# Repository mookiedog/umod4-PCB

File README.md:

# umod4-PCB

The Ultramod4 (A.K.A [umod4](https://github.com/mookiedog/umod4)) project is a real-time datalogger for Aprila Gen 1 ECUs.
It replaces the EPROM in an Aprila Gen 1 ECU with a circuit board that replaces the EPROM with a fast CPU that emulates an EPROM.
The EPROM emulation CPU's flash contains a special data logging firmware that the ECU will run.
The data-logging firmware is modified to send a real-time stream of ECU data to an interface on the umod4-PCB.
Software running in a daughterboard on the umod4-PCB combines the incoming ECU data stream with real-time GPS location and velocity information.
The combined data stream gets written to a logfile on a micro SD card.

The complete project is made up of:

* [umod4](https://github.com/mookiedog/umod4): the repository containing all the software that runs on the umod4-PCB.
* [UM4](https://github.com/mookiedog/umod4/tree/main/ecu/src): a special data logging firmware that runs inside the Gen1 ECU, currently resides inside the umod4 repository
* umod4-PCB: this repository, containing the PCB design files

The view below shows a top view of the 4V1a PCB, currently the most recent design.
The board's strange shape and cutout are mostly required to access ECU mounting points while avoiding interference with tall components on the ECU itself.

## PCB Status

The first version of the board (marked '4V0b' on its silkscreen) was fabricated at JCLPCB in 2022 and tested.
The second revision, the 4V1a board, was produced by JLCPCB in Jan 2025.
It incorporates all the workarounds from 4V0b, plus a number of changes and enhancements discovered over the last 18 months.
See the file [ChangeList.md](ChangeList.md) for the complete set of changes incorporated by 4V1.

The 4V1 version PCB has passed all its tests so far.

## Goals

### Design For Manufacture

This project uses a bare RP2040 chip to emulate the EPROM in a Gen 1 ECU.
The chip is too difficult for me to place by hand for reflowing the board using my [home-brew reflow](https://github.com/mookiedog/Reflow) process.
Instead, this PCB is designed for fabrication at JLCPCB.com.
Where possible, the BOM parts were chosen from JLCPCB's "basic" component list to avoid the fee for using an "extended" component.
Even so, stocks of "basic" parts fluctuate and components become obsolete, so the BOM might change with time to accomodate those changes.

Once any requirement for hand assembly was eliminated, the door was open to use smaller 0402 components on the PCB.

The initial version of the design (4V0b) has proven it can go end-to-end through the entire JCLPCB fabrication process where the resulting boards function as designed.

### Accessibility

I am not interested in making this project into a product that I would sell and support.
That said, it may be interesting enough for other Aprilia owners out there who have software and/or hardware skills that they might want to replicate the project for their own bike.

Who knows, it might be one of those things where a batch of boards gets made from time to time for people who are interested, feel like participating, and know that it is not a product.
Seriously, the last thing on earth that I want is someone sending me a note complaining that I haven't got WiFi working yet.

## Design Tool Choice

The project is currently developed using Cadsoft Eagle version 7.6, the last version I got years ago.
It's because I've used Eagle for the last bazillion years, and I own that old version outright.
These days, you are forced to forced to buy new versions of Eagle on a monthly subscription basis.
That doesn't work for me, because I make no money off this stuff and can't afford the subscription fees.
Too bad, I like Eagle.

I realize that at some point it would be worth switching the design over to something like KiCad to make it more accessible to the open source community.

Someday.

## Project Status

A ton of software exists, and a ton is left to write.

That said, the key to going for a ride though is that the fake EPROM on the circuit board needs to work. And it does!

Below, is a scope shot of the ECU performing memory cycles.
The top trace is the E clock generated by the ECU processor (a MC68HC11 variant).
The bottom trace is generated by the firmware that is pretending to be an EPROM.
The bottom trace goes high when the fake EPROM firmware reads the address and control signals from the HC11 memory bus.

If the memory cycle does not target the EPROM, the firmware drives the lower trace back to zero again very shortly after reading the address and control signal info.

If the memory cycle targets the EPROM with a read operation, the firmware takes a bit more time to access the proper memory byte corresponding to the desired EPROM memory byte, then drive that data onto the memory bus.
The lower scope trace gets driven low again to indicate the time that the read data is available on the memory bus.

Finally, if the memory cycle targets the EPROM with a write, the firmware is required to wait even longer for the write data to finally appear on the bus.
The fake EPROM firmware drives the lower trace back to zero to indicate the exact time that it samples the write data off the HC11 memory bus.

Given that all of these operations are going on all the time, the lower trace has been set up so that it shows examples of the three different operations (ignore, read, write) superimposed on each other:

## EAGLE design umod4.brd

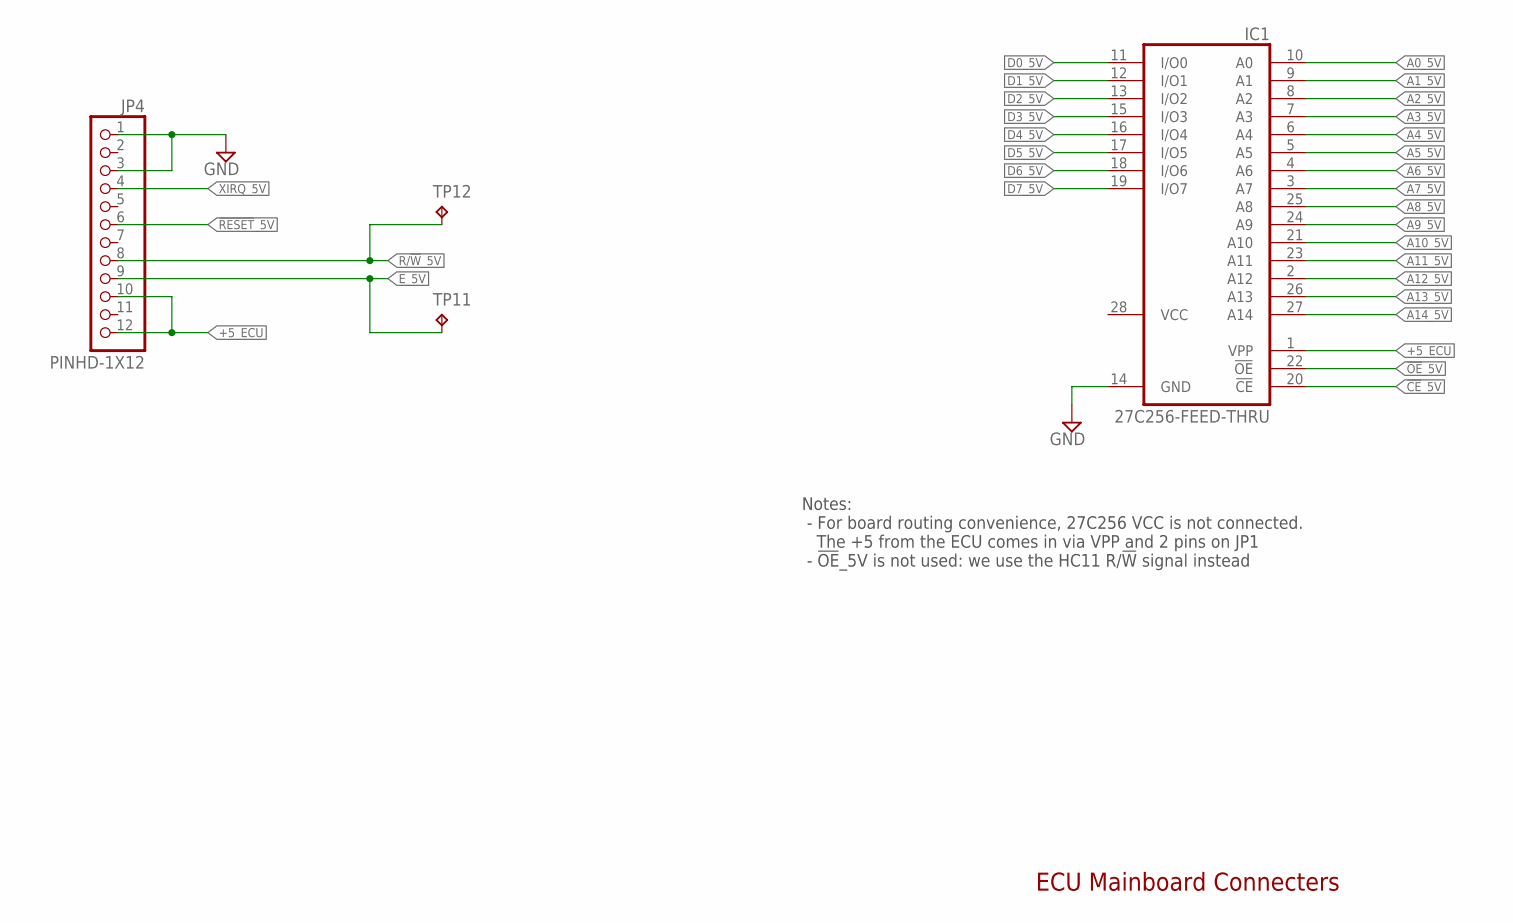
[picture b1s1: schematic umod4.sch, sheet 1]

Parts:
IC1: 27C256-FEED-THRU; DIL28-6
JP4: PINHD-1X12; 1X12
TP11, TP12: 1035; KEYSTONE-1035

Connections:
!CE!_5V: IC1.20 (!CE); also elsewhere on the board
!OE!_5V: IC1.22 (!OE)
!RESET!_5V: JP4.6; also elsewhere on the board
+5_ECU: IC1.1 (VPP), JP4.10, JP4.12; also elsewhere on the board
A0_5V: IC1.10 (A0); also elsewhere on the board
A1_5V: IC1.9 (A1); also elsewhere on the board
A2_5V: IC1.8 (A2); also elsewhere on the board
A3_5V: IC1.7 (A3); also elsewhere on the board
A4_5V: IC1.6 (A4); also elsewhere on the board
A5_5V: IC1.5 (A5); also elsewhere on the board
A6_5V: IC1.4 (A6); also elsewhere on the board
A7_5V: IC1.3 (A7); also elsewhere on the board
A8_5V: IC1.25 (A8); also elsewhere on the board
A9_5V: IC1.24 (A9); also elsewhere on the board
A10_5V: IC1.21 (A10); also elsewhere on the board
A11_5V: IC1.23 (A11); also elsewhere on the board
A12_5V: IC1.2 (A12); also elsewhere on the board
A13_5V: IC1.26 (A13); also elsewhere on the board
A14_5V: IC1.27 (A14); also elsewhere on the board
D0_5V: IC1.11 (I/O0); also elsewhere on the board
D1_5V: IC1.12 (I/O1); also elsewhere on the board
D2_5V: IC1.13 (I/O2); also elsewhere on the board
D3_5V: IC1.15 (I/O3); also elsewhere on the board
D4_5V: IC1.16 (I/O4); also elsewhere on the board
D5_5V: IC1.17 (I/O5); also elsewhere on the board
D6_5V: IC1.18 (I/O6); also elsewhere on the board
D7_5V: IC1.19 (I/O7); also elsewhere on the board
E_5V: JP4.9, TP11.P$1; also elsewhere on the board
GND: IC1.14 (GND), JP4.1, JP4.3; also elsewhere on the board
R/!W!_5V: JP4.8, TP12.P$1; also elsewhere on the board
VCC: IC1.28 (VCC)
XIRQ_5V: JP4.4

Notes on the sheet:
ECU Mainboard Connecters
Notes: - For board routing convenience, 27C256 VCC is not connected. The +5 from the ECU comes in via VPP and 2 pins on JP1 - !OE!_5V is not used: we use the HC11 R/!W! signal instead

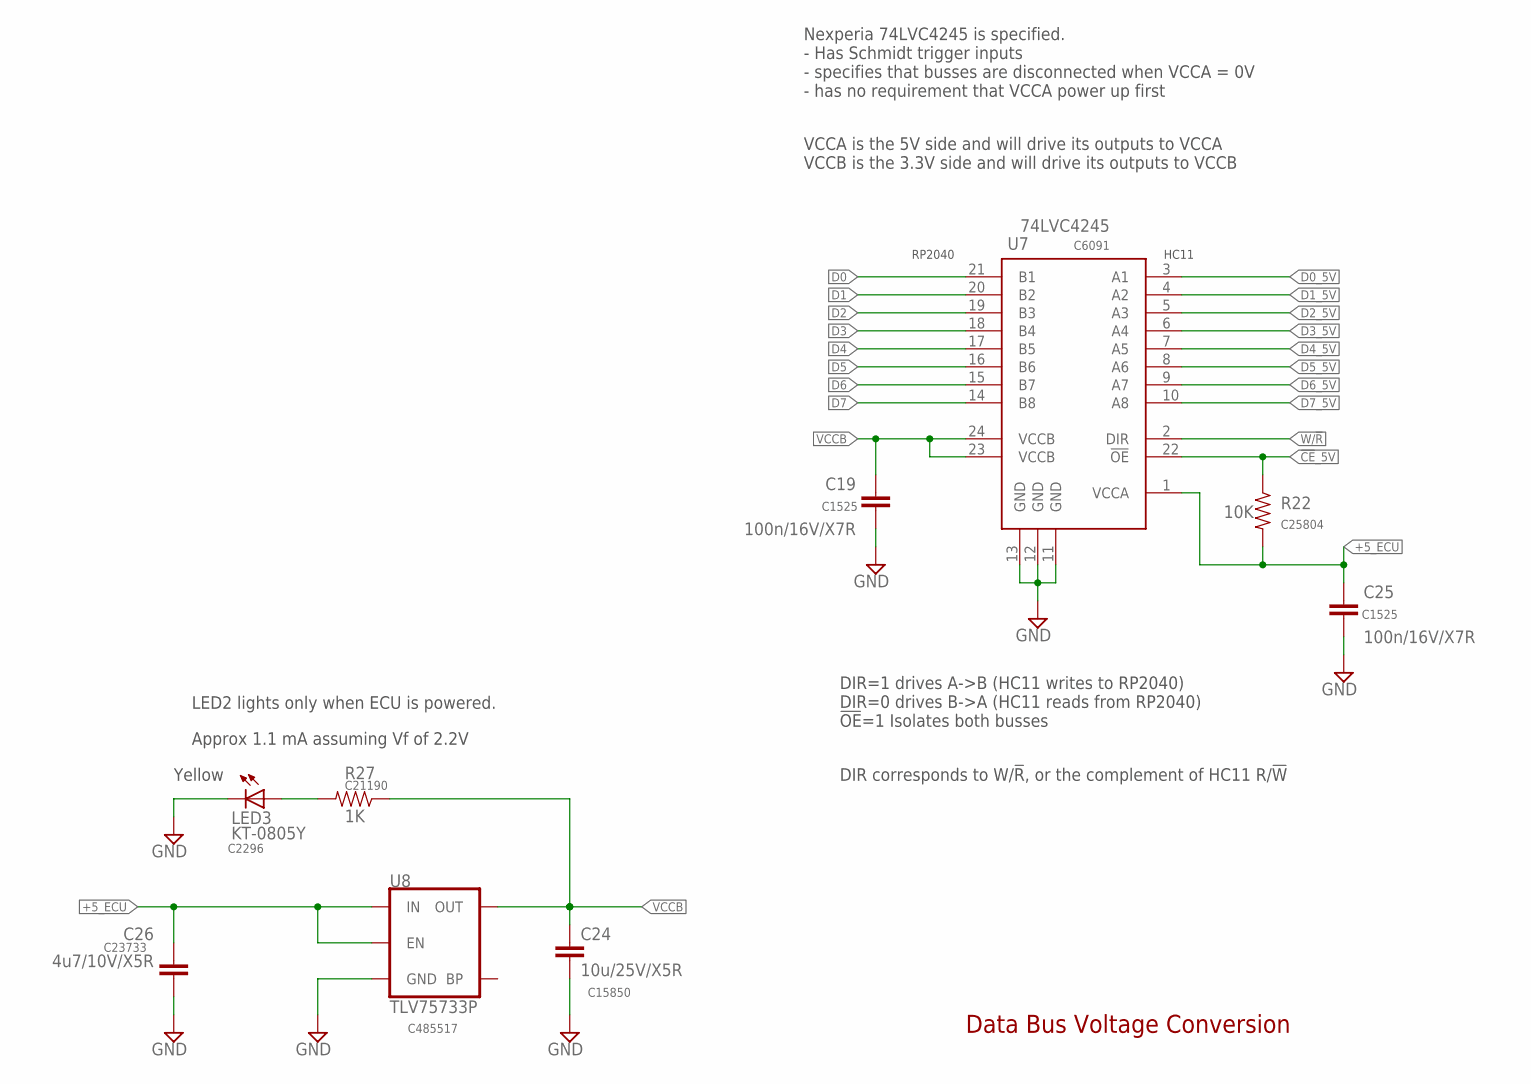
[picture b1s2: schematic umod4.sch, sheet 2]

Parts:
C19, C25: 100n/16V/X7R; SMD-0402-NOM; LCSC_PART C1525
C24: 10u/25V/X5R; SMD-0805-NOM; LCSC_PART C15850
C26: 4u7/10V/X5R; SMD-0402-NOM; LCSC_PART C23733
LED3: KT-0805Y; SML0805; LCSC_PART C2296
R22: 10K; SMD-0603-NOM; LCSC_PART C25804
R27: 1K; SMD-0603-NOM; LCSC_PART C21190
U7: 74LVC4245; TSSOP-24; LCSC_PART C6091
U8: TLV75733P; SOT23-5; LCSC_PART C485517

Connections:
!CE!_5V: R22.1, U7.22 (!OE); also elsewhere on the board
+5_ECU: C25.1, C26.1, R22.2, U7.1 (VCCA), U8.1 (IN), U8.3 (EN); also elsewhere on the board
D0: U7.21 (B1); also elsewhere on the board
D0_5V: U7.3 (A1); also elsewhere on the board
D1: U7.20 (B2); also elsewhere on the board
D1_5V: U7.4 (A2); also elsewhere on the board
D2: U7.19 (B3); also elsewhere on the board
D2_5V: U7.5 (A3); also elsewhere on the board
D3: U7.18 (B4); also elsewhere on the board
D3_5V: U7.6 (A4); also elsewhere on the board
D4: U7.17 (B5); also elsewhere on the board
D4_5V: U7.7 (A5); also elsewhere on the board
D5: U7.16 (B6); also elsewhere on the board
D5_5V: U7.8 (A6); also elsewhere on the board
D6: U7.15 (B7); also elsewhere on the board
D6_5V: U7.9 (A7); also elsewhere on the board
D7: U7.14 (B8); also elsewhere on the board
D7_5V: U7.10 (A8); also elsewhere on the board
GND: C19.2, C24.2, C25.2, C26.2, LED3.C, U7.11 (GND), U7.12 (GND), U7.13 (GND), U8.2 (GND); also elsewhere on the board
unnamed: LED3.A, R27.2
VCCB: C19.1, C24.1, R27.1, U7.23 (VCCB), U7.24 (VCCB), U8.5 (OUT); also elsewhere on the board
W/!R!: U7.2 (DIR); also elsewhere on the board

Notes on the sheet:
Data Bus Voltage Conversion
DIR=1 drives A->B (HC11 writes to RP2040) DIR=0 drives B->A (HC11 reads from RP2040) !OE!=1 Isolates both busses
VCCA is the 5V side and will drive its outputs to VCCA VCCB is the 3.3V side and will drive its outputs to VCCB
DIR corresponds to W/!R!, or the complement of HC11 R/!W!
RP2040
HC11
Nexperia 74LVC4245 is specified. - Has Schmidt trigger inputs - specifies that busses are disconnected when VCCA = 0V - has no requirement that VCCA power up first
Yellow
Approx 1.1 mA assuming Vf of 2.2V
LED2 lights only when ECU is powered.

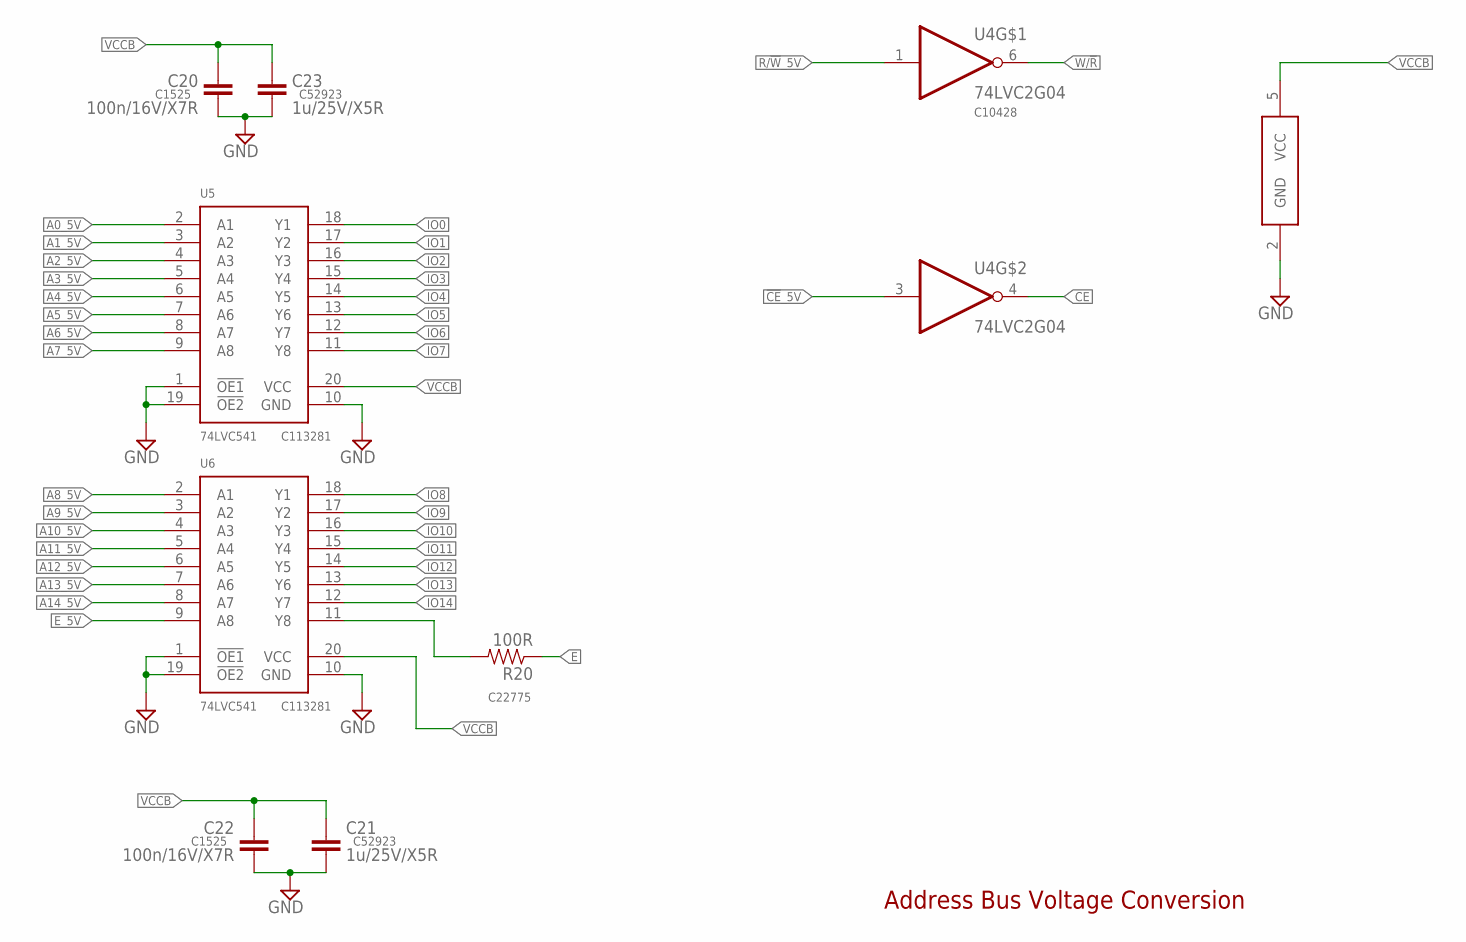
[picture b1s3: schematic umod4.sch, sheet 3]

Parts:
C20, C22: 100n/16V/X7R; SMD-0402-NOM; LCSC_PART C1525
C21, C23: 1u/25V/X5R; SMD-0402-NOM; LCSC_PART C52923
R20: 100R; SMD-0603-NOM; LCSC_PART C22775
U4: 74LVC2G04; SOT23-6; LCSC_PART C10428
U5, U6: 74LVC541; TSSOP-20; LCSC_PART C113281

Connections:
!CE!_5V: U4.3 (I); also elsewhere on the board
A0_5V: U5.2 (A1); also elsewhere on the board
A1_5V: U5.3 (A2); also elsewhere on the board
A2_5V: U5.4 (A3); also elsewhere on the board
A3_5V: U5.5 (A4); also elsewhere on the board
A4_5V: U5.6 (A5); also elsewhere on the board
A5_5V: U5.7 (A6); also elsewhere on the board
A6_5V: U5.8 (A7); also elsewhere on the board
A7_5V: U5.9 (A8); also elsewhere on the board
A8_5V: U6.2 (A1); also elsewhere on the board
A9_5V: U6.3 (A2); also elsewhere on the board
A10_5V: U6.4 (A3); also elsewhere on the board
A11_5V: U6.5 (A4); also elsewhere on the board
A12_5V: U6.6 (A5); also elsewhere on the board
A13_5V: U6.7 (A6); also elsewhere on the board
A14_5V: U6.8 (A7); also elsewhere on the board
CE: U4.4 (O); also elsewhere on the board
E: R20.1; also elsewhere on the board
E_5V: U6.9 (A8); also elsewhere on the board
GND: C20.2, C21.2, C22.2, C23.2, U4.2 (GND), U5.1 (!OE1), U5.10 (GND), U5.19 (!OE2), U6.1 (!OE1), U6.10 (GND), U6.19 (!OE2); also elsewhere on the board
IO0: U5.18 (Y1); also elsewhere on the board
IO1: U5.17 (Y2); also elsewhere on the board
IO2: U5.16 (Y3); also elsewhere on the board
IO3: U5.15 (Y4); also elsewhere on the board
IO4: U5.14 (Y5); also elsewhere on the board
IO5: U5.13 (Y6); also elsewhere on the board
IO6: U5.12 (Y7); also elsewhere on the board
IO7: U5.11 (Y8); also elsewhere on the board
IO8: U6.18 (Y1); also elsewhere on the board
IO9: U6.17 (Y2); also elsewhere on the board
IO10: U6.16 (Y3); also elsewhere on the board
IO11: U6.15 (Y4); also elsewhere on the board
IO12: U6.14 (Y5); also elsewhere on the board
IO13: U6.13 (Y6); also elsewhere on the board
IO14: U6.12 (Y7); also elsewhere on the board
unnamed: R20.2, U6.11 (Y8)
R/!W!_5V: U4.1 (I); also elsewhere on the board
VCCB: C20.1, C21.1, C22.1, C23.1, U4.5 (VCC), U5.20 (VCC), U6.20 (VCC); also elsewhere on the board
W/!R!: U4.6 (O); also elsewhere on the board

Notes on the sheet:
Address Bus Voltage Conversion

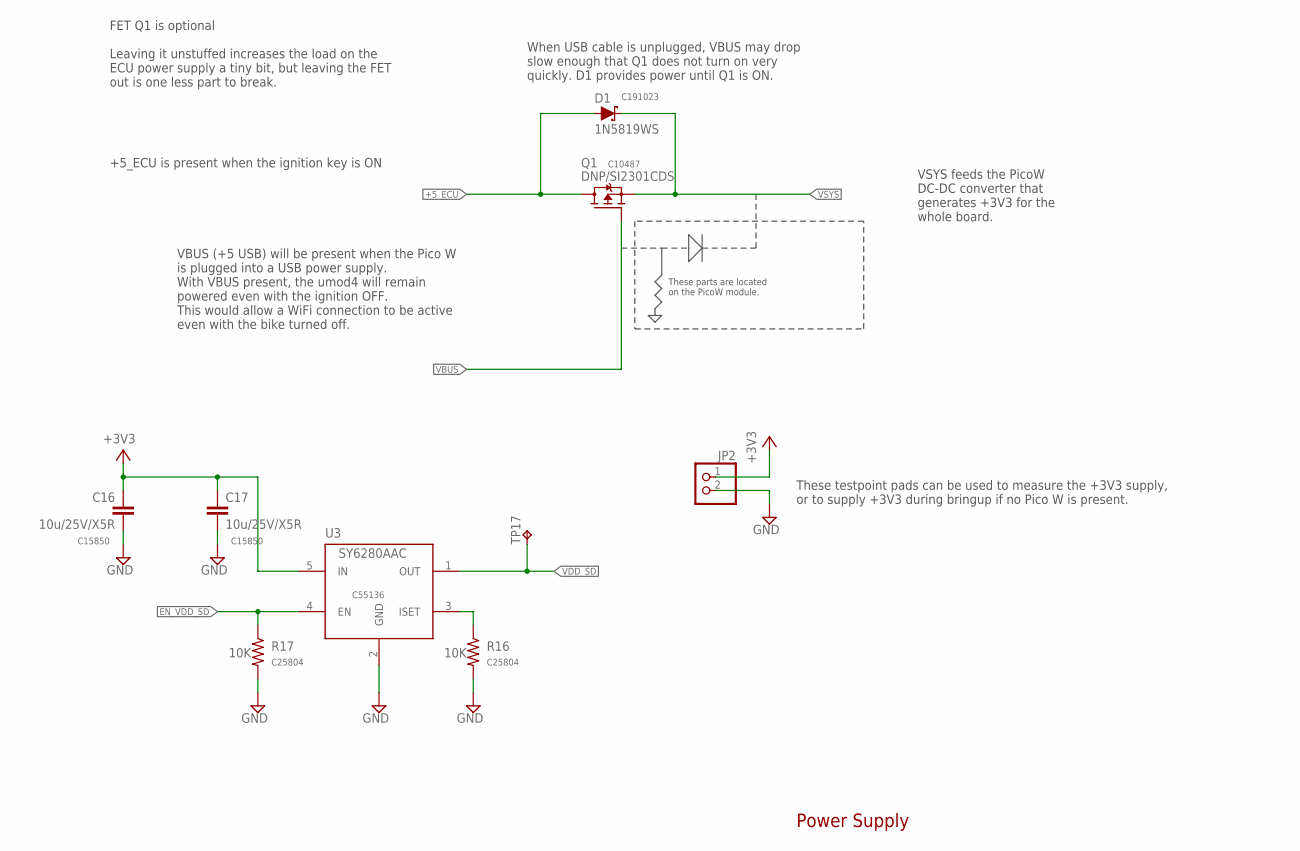
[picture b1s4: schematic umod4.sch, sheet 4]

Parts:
C16, C17: 10u/25V/X5R; SMD-0805-NOM; LCSC_PART C15850
D1: 1N5819WS; SOD-323; LCSC_PART C191023
JP2: PINHD-1X2; 1X02
Q1: DNP/SI2301CDS; SOT23
R16, R17: 10K; SMD-0603-NOM; LCSC_PART C25804
TP17: 1035; KEYSTONE-1035
U3: SY6280AAC; SOT23-5; LCSC_PART C55136

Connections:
+3V3: C16.1, C17.1, JP2.1, U3.5 (IN); also elsewhere on the board
+5_ECU: D1.A, Q1.D; also elsewhere on the board
EN_VDD_SD: R17.1, U3.4 (EN); also elsewhere on the board
GND: C16.2, C17.2, JP2.2, R16.2, R17.2, U3.2 (GND); also elsewhere on the board
unnamed: R16.1, U3.3 (ISET)
VBUS: Q1.G; also elsewhere on the board
VDD_SD: TP17.P$1, U3.1 (OUT); also elsewhere on the board
VSYS: D1.C, Q1.S; also elsewhere on the board

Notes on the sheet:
Power Supply
VSYS feeds the PicoW DC-DC converter that generates +3V3 for the whole board.
These parts are located on the PicoW module.
These testpoint pads can be used to measure the +3V3 supply, or to supply +3V3 during bringup if no Pico W is present.
When USB cable is unplugged, VBUS may drop slow enough that Q1 does not turn on very quickly. D1 provides power until Q1 is ON.
+5_ECU is present when the ignition key is ON
VBUS (+5 USB) will be present when the Pico W is plugged into a USB power supply. With VBUS present, the umod4 will remain powered even with the ignition OFF. This would allow a WiFi connection to be active even with the bike turned off.
FET Q1 is optional Leaving it unstuffed increases the load on the ECU power supply a tiny bit, but leaving the FET out is one less part to break.

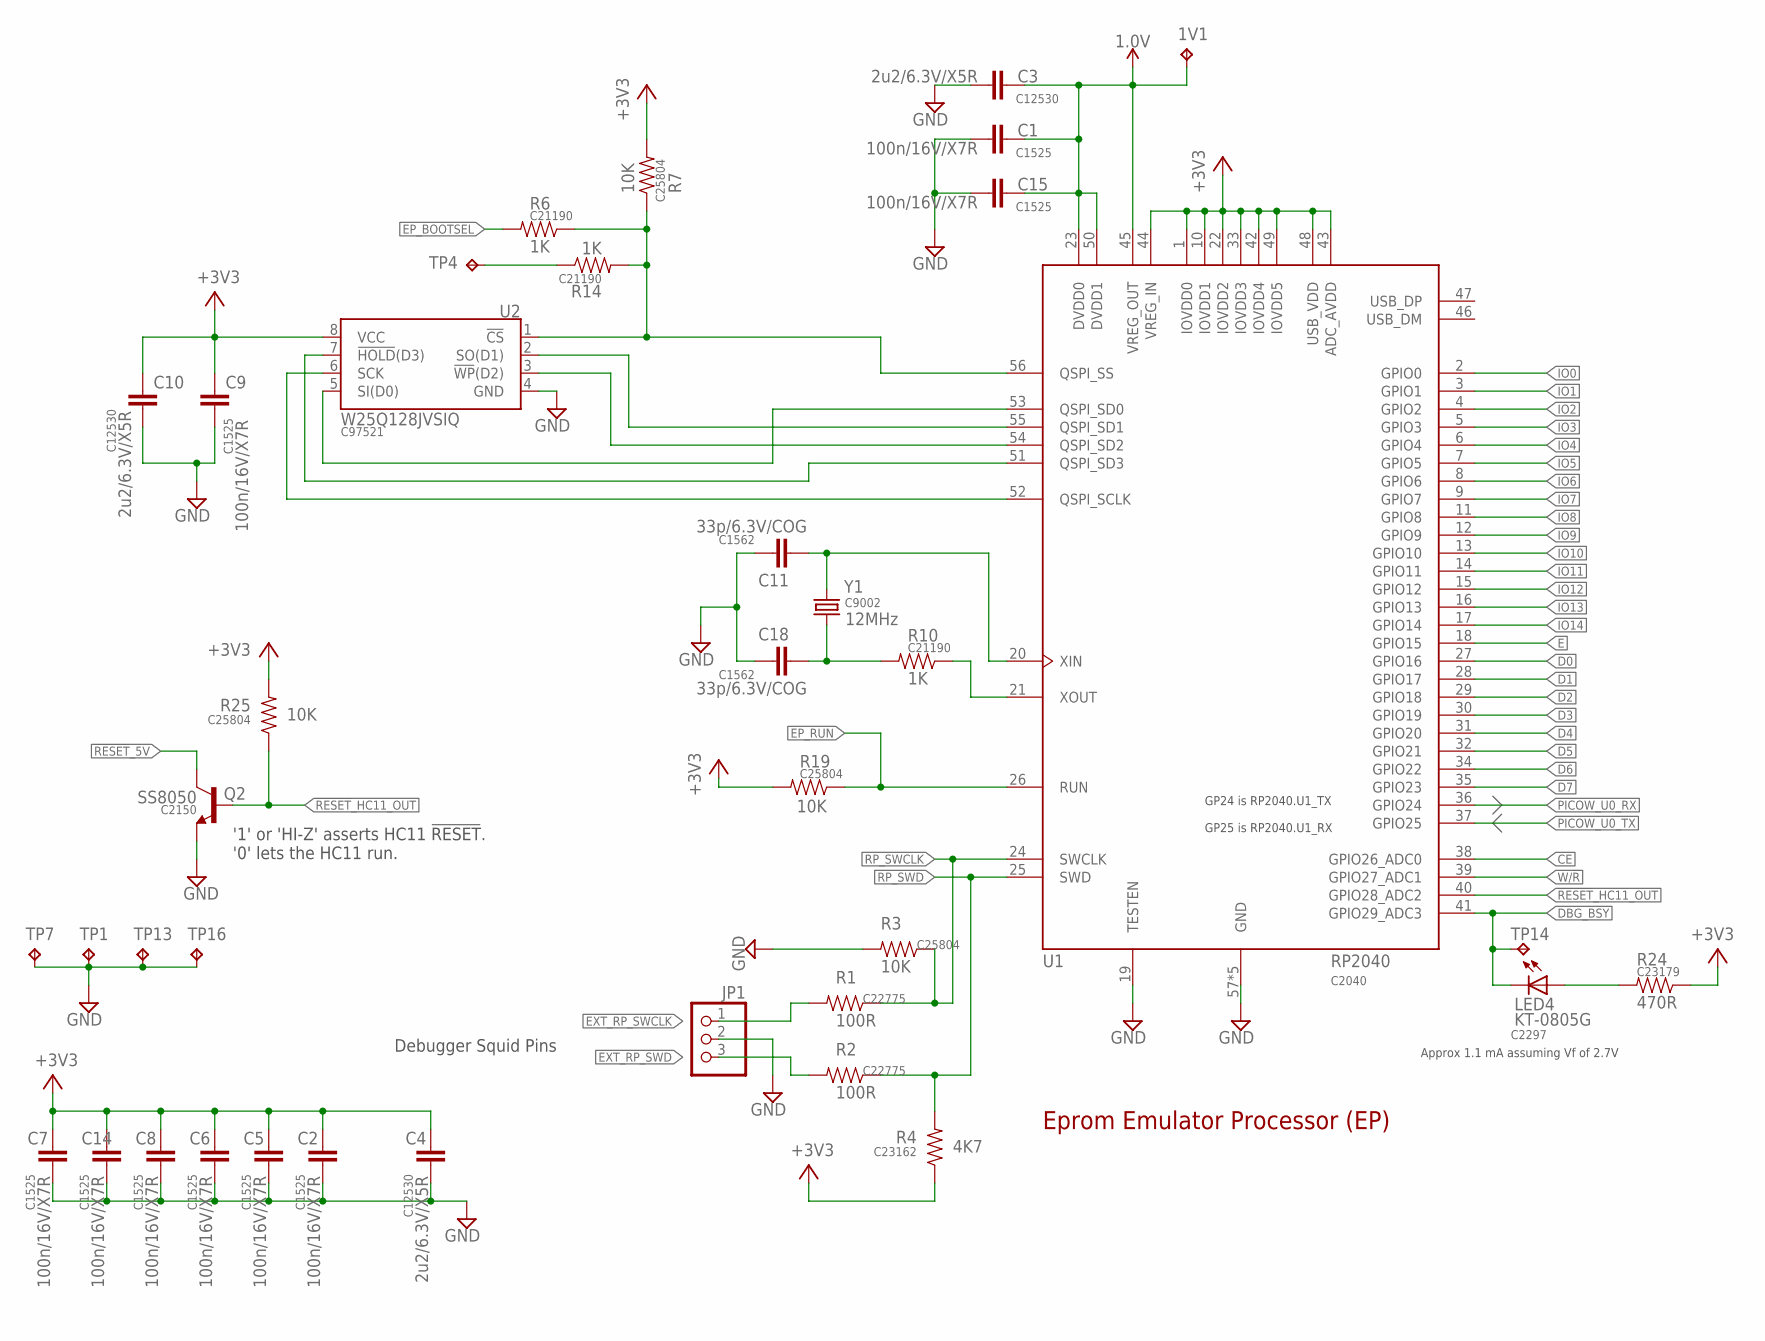
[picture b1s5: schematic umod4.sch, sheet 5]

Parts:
1V1: TPB1,27; B1,27
C1, C2, C5, C6, C7, C8, C9, C14, C15: 100n/16V/X7R; SMD-0402-NOM; LCSC_PART C1525
C3, C4, C10: 2u2/6.3V/X5R; SMD-0402-NOM; LCSC_PART C12530
C11, C18: 33p/6.3V/COG; SMD-0402-NOM; LCSC_PART C1562
JP1: PINHD-1X3; 1X03
LED4: KT-0805G; SML0805; LCSC_PART C2297
Q2: SS8050; SOT23-3; LCSC_PART C2150
R1, R2: 100R; SMD-0603-NOM; LCSC_PART C22775
R3, R7, R19, R25: 10K; SMD-0603-NOM; LCSC_PART C25804
R4: 4K7; SMD-0603-NOM; LCSC_PART C23162
R6, R10, R14: 1K; SMD-0603-NOM; LCSC_PART C21190
R24: 470R; SMD-0603-NOM; LCSC_PART C23179
TP1, TP4, TP7, TP13, TP14, TP16: 1035; KEYSTONE-1035
U1: RP2040; RP2040-QFN56; LCSC_PART C2040
U2: W25Q128JVSIQ; SOIC-8; LCSC_PART C97521
Y1: 12MHz; CRYSTAL-SMD-3.2X2.5MM; LCSC_PART C9002

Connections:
1.0V: 1V1.TP, C1.1, C3.1, C15.1, U1.23 (DVDD0), U1.45 (VREG_OUT), U1.50 (DVDD1)
!RESET!_5V: Q2.3 (C); also elsewhere on the board
!RESET!_HC11_OUT: Q2.1 (B), R25.1, U1.40 (GPIO28_ADC2)
+3V3: C2.1, C4.1, C5.1, C6.1, C7.1, C8.1, C9.1, C10.1, C14.1, R4.1, R7.2, R19.2, R24.1, R25.2, U1.1 (IOVDD0), U1.10 (IOVDD1), U1.22 (IOVDD2), U1.33 (IOVDD3), U1.42 (IOVDD4), U1.43 (ADC_AVDD), U1.44 (VREG_IN), U1.48 (USB_VDD), U1.49 (IOVDD5), U2.8 (VCC); also elsewhere on the board
CE: U1.38 (GPIO26_ADC0); also elsewhere on the board
D0: U1.27 (GPIO16); also elsewhere on the board
D1: U1.28 (GPIO17); also elsewhere on the board
D2: U1.29 (GPIO18); also elsewhere on the board
D3: U1.30 (GPIO19); also elsewhere on the board
D4: U1.31 (GPIO20); also elsewhere on the board
D5: U1.32 (GPIO21); also elsewhere on the board
D6: U1.34 (GPIO22); also elsewhere on the board
D7: U1.35 (GPIO23); also elsewhere on the board
DBG_BSY: LED4.C, TP14.P$1, U1.41 (GPIO29_ADC3)
E: U1.18 (GPIO15); also elsewhere on the board
EP_BOOTSEL: R6.2; also elsewhere on the board
EP_RUN: R19.1, U1.26 (RUN); also elsewhere on the board
EXT_RP_SWCLK: JP1.1, R1.2
EXT_RP_SWD: JP1.3, R2.2
GND: C1.2, C2.2, C3.2, C4.2, C5.2, C6.2, C7.2, C8.2, C9.2, C10.2, C11.1, C14.2, C15.2, C18.1, JP1.2, Q2.2 (E), R3.2, TP1.P$1, TP7.P$1, TP13.P$1, TP16.P$1, U1.19 (TESTEN), U1.57 (GND), U1.GND@1 (GND), U1.GND@2 (GND), U1.GND@3 (GND), U1.GND@4 (GND), U2.4 (GND); also elsewhere on the board
IO0: U1.2 (GPIO0); also elsewhere on the board
IO1: U1.3 (GPIO1); also elsewhere on the board
IO2: U1.4 (GPIO2); also elsewhere on the board
IO3: U1.5 (GPIO3); also elsewhere on the board
IO4: U1.6 (GPIO4); also elsewhere on the board
IO5: U1.7 (GPIO5); also elsewhere on the board
IO6: U1.8 (GPIO6); also elsewhere on the board
IO7: U1.9 (GPIO7); also elsewhere on the board
IO8: U1.11 (GPIO8); also elsewhere on the board
IO9: U1.12 (GPIO9); also elsewhere on the board
IO10: U1.13 (GPIO10); also elsewhere on the board
IO11: U1.14 (GPIO11); also elsewhere on the board
IO12: U1.15 (GPIO12); also elsewhere on the board
IO13: U1.16 (GPIO13); also elsewhere on the board
IO14: U1.17 (GPIO14); also elsewhere on the board
unnamed: C18.2, R10.2, Y1.1
unnamed: C11.2, U1.20 (XIN), Y1.3 (2)
unnamed: R14.1, TP4.P$1
unnamed: R10.1, U1.21 (XOUT)
unnamed: LED4.A, R24.2
unnamed: R6.1, R7.1, R14.2, U1.56 (QSPI_SS), U2.1 (!CS!)
unnamed: U1.52 (QSPI_SCLK), U2.6 (SCK)
unnamed: U1.53 (QSPI_SD0), U2.5 (SI(D0))
unnamed: U1.55 (QSPI_SD1), U2.2 (SO(D1))
unnamed: U1.54 (QSPI_SD2), U2.3 (!WP!(D2))
unnamed: U1.51 (QSPI_SD3), U2.7 (!HOLD!(D3))
PICOW_U0_RX: U1.36 (GPIO24); also elsewhere on the board
PICOW_U0_TX: U1.37 (GPIO25); also elsewhere on the board
RP_SWCLK: R1.1, R3.1, U1.24 (SWCLK); also elsewhere on the board
RP_SWD: R2.1, R4.2, U1.25 (SWD); also elsewhere on the board
W/!R!: U1.39 (GPIO27_ADC1); also elsewhere on the board

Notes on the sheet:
Eprom Emulator Processor (EP)
Approx 1.1 mA assuming Vf of 2.7V
GP24 is RP2040.U1_TX
GP25 is RP2040.U1_RX
'1' or 'HI-Z' asserts HC11 !RESET!. '0' lets the HC11 run.
Debugger Squid Pins

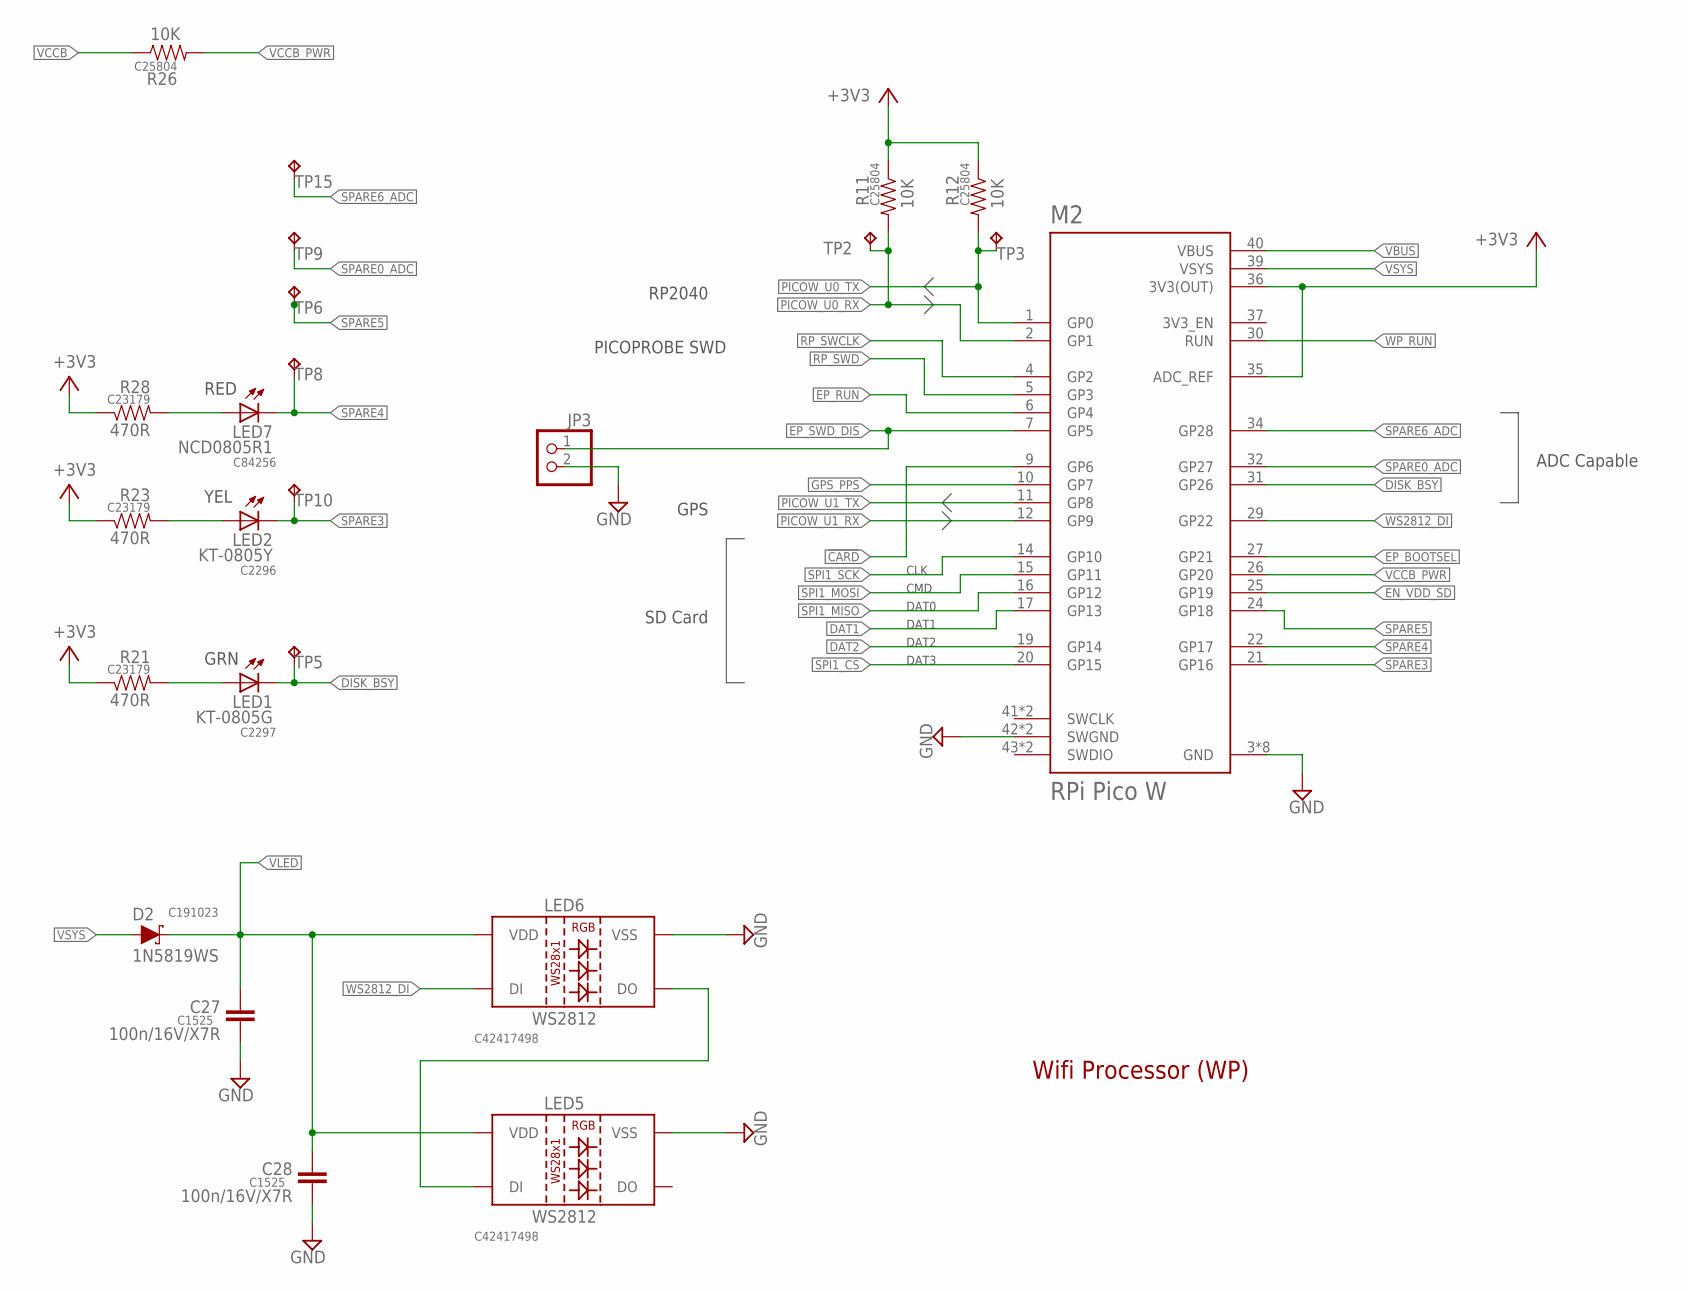
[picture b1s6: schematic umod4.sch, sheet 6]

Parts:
C27, C28: 100n/16V/X7R; SMD-0402-NOM; LCSC_PART C1525
D2: 1N5819WS; SOD-323; LCSC_PART C191023
JP3: PINHD-1X2; 1X02
LED1: KT-0805G; SML0805; LCSC_PART C2297
LED2: KT-0805Y; SML0805; LCSC_PART C2296
LED5, LED6: WS2812; WS2812B; LCSC_PART C42417498
LED7: NCD0805R1; SML0805; LCSC_PART C84256
M2: RPi Pico W; PICO-TH
R11, R12, R26: 10K; SMD-0603-NOM; LCSC_PART C25804
R21, R23, R28: 470R; SMD-0603-NOM; LCSC_PART C23179
TP2, TP3, TP5, TP6, TP8, TP9, TP10, TP15: 1035; KEYSTONE-1035

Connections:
!CARD: M2.9 (GP6); also elsewhere on the board
+3V3: M2.35 (ADC_REF), M2.36 (3V3(OUT)), R11.1, R12.1, R21.1, R23.1, R28.1; also elsewhere on the board
DAT1: M2.17 (GP13); also elsewhere on the board
DAT2: M2.19 (GP14); also elsewhere on the board
DISK_BSY: LED1.C, M2.31 (GP26), TP5.P$1
EN_VDD_SD: M2.25 (GP19); also elsewhere on the board
EP_BOOTSEL: M2.27 (GP21); also elsewhere on the board
EP_RUN: M2.6 (GP4); also elsewhere on the board
EP_SWD_DIS: JP3.1, M2.7 (GP5)
GND: C27.2, C28.2, JP3.2, LED5.3 (VSS), LED6.3 (VSS), M2.3 (GND), M2.8 (GND), M2.13 (GND), M2.18 (GND), M2.23 (GND), M2.28 (GND), M2.33 (GND), M2.38 (GND), M2.42 (SWGND), M2.45 (SWGND); also elsewhere on the board
GPS_PPS: M2.10 (GP7); also elsewhere on the board
unnamed: LED2.A, R23.2
unnamed: LED5.4 (DI), LED6.2 (DO)
unnamed: LED1.A, R21.2
unnamed: LED7.A, R28.2
PICOW_U0_RX: M2.2 (GP1), R11.2, TP2.P$1; also elsewhere on the board
PICOW_U0_TX: M2.1 (GP0), R12.2, TP3.P$1; also elsewhere on the board
PICOW_U1_RX: M2.12 (GP9); also elsewhere on the board
PICOW_U1_TX: M2.11 (GP8); also elsewhere on the board
RP_SWCLK: M2.4 (GP2); also elsewhere on the board
RP_SWD: M2.5 (GP3); also elsewhere on the board
SPARE0_ADC: M2.32 (GP27), TP9.P$1
SPARE3: LED2.C, M2.21 (GP16), TP10.P$1
SPARE4: LED7.C, M2.22 (GP17), TP8.P$1
SPARE5: M2.24 (GP18), TP6.P$1
SPARE6_ADC: M2.34 (GP28), TP15.P$1
SPI1_CS: M2.20 (GP15); also elsewhere on the board
SPI1_MISO: M2.16 (GP12); also elsewhere on the board
SPI1_MOSI: M2.15 (GP11); also elsewhere on the board
SPI1_SCK: M2.14 (GP10); also elsewhere on the board
VBUS: M2.40 (VBUS); also elsewhere on the board
VCCB: R26.1; also elsewhere on the board
VCCB_PWR: M2.26 (GP20), R26.2
VLED: C27.1, C28.1, D2.C, LED5.1 (VDD), LED6.1 (VDD)
VSYS: D2.A, M2.39 (VSYS); also elsewhere on the board
WP_RUN: M2.30 (RUN)
WS2812_DI: LED6.4 (DI), M2.29 (GP22)

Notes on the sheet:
Wifi Processor (WP)
GPS
PICOPROBE SWD
RP2040
SD Card
DAT0
DAT1
DAT2
DAT3
CMD
CLK
ADC Capable
RED
YEL
GRN

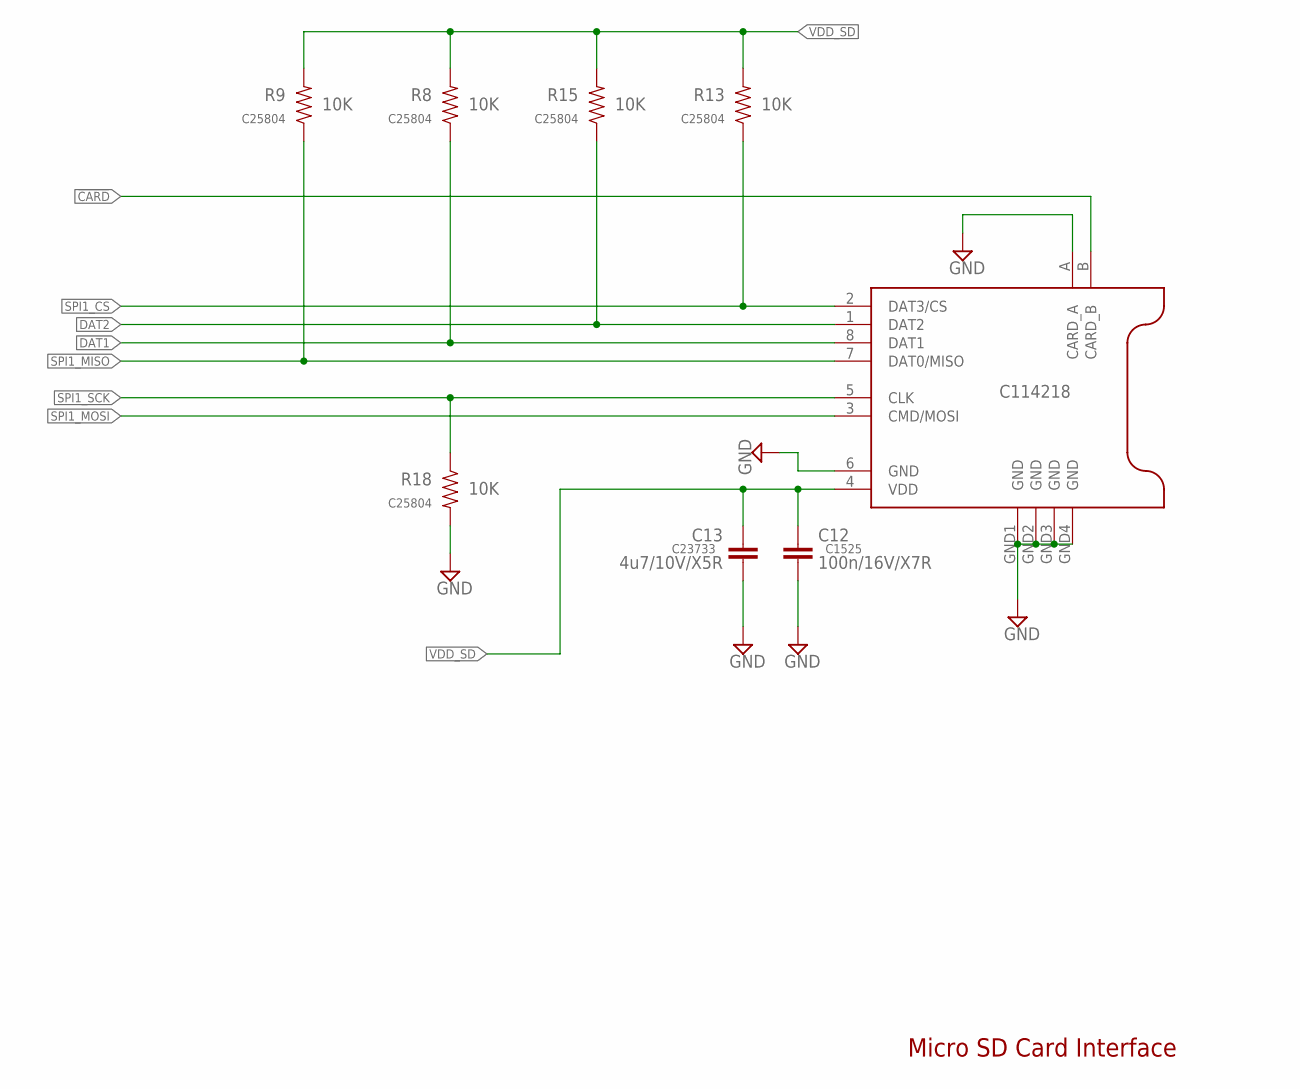
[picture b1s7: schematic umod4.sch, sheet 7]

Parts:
C12: 100n/16V/X7R; SMD-0402-NOM; LCSC_PART C1525
C13: 4u7/10V/X5R; SMD-0402-NOM; LCSC_PART C23733
R8, R9, R13, R15, R18: 10K; SMD-0603-NOM; LCSC_PART C25804
SD1: DM3AT-SF-PEJM5; DM3AT; LCSC_PART C114218

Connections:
!CARD: SD1.B (CARD_B); also elsewhere on the board
DAT1: R8.1, SD1.8 (DAT1); also elsewhere on the board
DAT2: R15.1, SD1.1 (DAT2); also elsewhere on the board
GND: C12.2, C13.2, R18.2, SD1.6 (GND), SD1.A (CARD_A), SD1.GND1 (GND), SD1.GND2 (GND), SD1.GND3 (GND), SD1.GND4 (GND); also elsewhere on the board
SPI1_CS: R13.1, SD1.2 (DAT3/CS); also elsewhere on the board
SPI1_MISO: R9.1, SD1.7 (DAT0/MISO); also elsewhere on the board
SPI1_MOSI: SD1.3 (CMD/MOSI); also elsewhere on the board
SPI1_SCK: R18.1, SD1.5 (CLK); also elsewhere on the board
VDD_SD: C12.1, C13.1, R8.2, R9.2, R13.2, R15.2, SD1.4 (VDD); also elsewhere on the board

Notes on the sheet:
Micro SD Card Interface

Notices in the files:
parts and their libraries:
SparkFun-Clocks: Licensing: Creative Commons ShareAlike 4.0 International - https://creativecommons.org/licenses/by-sa/4.0
